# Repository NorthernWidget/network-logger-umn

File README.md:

Logger
======
This code is heavily based off the the Alog library by Northern Widget. When
completed, this implementation will include radio telemetry using the RFM69 chip
for RF communication. This library is currently a work in progress and should
not be expected to work on its own. Expect a working copy in early May.
The new libraries in this repo are the Network.* files.
-Luke Cesarz

Data logger library for the Arduino-based ALog (http://northernwidget.com/?page_id=8)

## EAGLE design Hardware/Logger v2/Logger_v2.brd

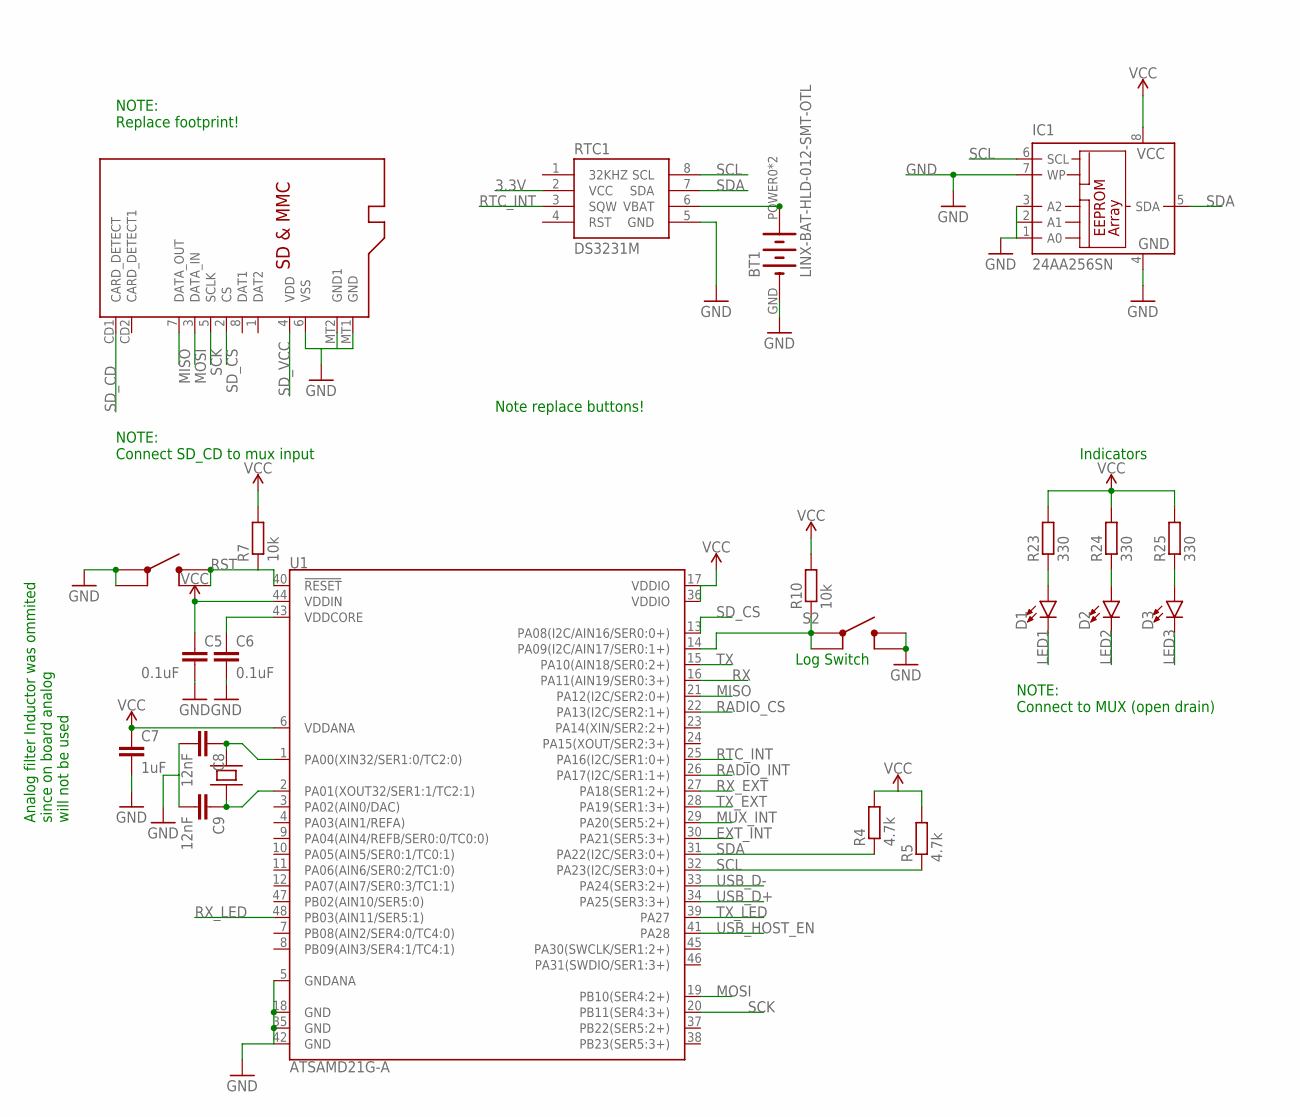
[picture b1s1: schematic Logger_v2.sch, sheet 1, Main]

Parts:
BT1: LINX-BAT-HLD-012-SMT-OTL; LINX_BAT-HLD-012-SMT
C5, C6: 0.1uF; C0603
C7: 1uF; C0603
C8, C9: 12nF; C0603
D1, D2, D3: LED0603; LED-0603
IC1: 24AA256SN; SO-08
R4, R5: 4.7k; R0603
R7, R10: 10k; R0603
R23, R24, R25: 330; R0603
RTC1: DS3231M; SO08
S2: SKRPABE010; SKRPABE010_(SWITCH)
U1: ATSAMD21G-A; TQFP-48
U$1: SKRPABE010; SKRPABE010_(SWITCH)
U$2: MICROSD
U$5: CM200; 4-SOJ

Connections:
3.3V: C5.1, C7.1, IC1.8 (VCC), R4.2, R5.2, R7.2, R10.2, R23.2, R24.2, R25.2, RTC1.2 (VCC), U1.6 (VDDANA), U1.17 (VDDIO), U1.36 (VDDIO), U1.44 (VDDIN); also elsewhere on the board
EXT_INT: U1.30 (PA21(SER5:3+)); also elsewhere on the board
GND: BT1.GND (-), C5.2, C6.2, C7.2, C8.2, C9.2, IC1.1 (A0), IC1.2 (A1), IC1.3 (A2), IC1.4 (GND), IC1.7 (WP), RTC1.5 (GND), S2.P$3 (3), S2.P$4 (4), U1.5 (GNDANA), U1.18 (GND), U1.35 (GND), U1.42 (GND), U$1.P$1 (1), U$1.P$2 (2), U$2.6 (VSS), U$2.MT1 (GND), U$2.MT2 (GND1); also elsewhere on the board
LED1: D1.C; also elsewhere on the board
LED2: D2.C; also elsewhere on the board
LED3: D3.C; also elsewhere on the board
MISO: U1.21 (PA12(I2C/SER2:0+)), U$2.7 (DATA_OUT); also elsewhere on the board
MOSI: U1.19 (PB10(SER4:2+)), U$2.3 (DATA_IN); also elsewhere on the board
MUX_INT: U1.29 (PA20(SER5:2+)); also elsewhere on the board
unnamed: R10.1, S2.P$1 (1), S2.P$2 (2), U1.14 (PA09(I2C/AIN17/SER0:1+))
unnamed: C6.1, U1.43 (VDDCORE)
unnamed: C8.1, U1.1 (PA00(XIN32/SER1:0/TC2:0)), U$5.P$4
unnamed: C9.1, U1.2 (PA01(XOUT32/SER1:1/TC2:1)), U$5.P$1
unnamed: BT1.POWER0 (+), BT1.POWER1 (+), RTC1.6 (VBAT)
unnamed: D1.A, R23.1
unnamed: D2.A, R24.1
unnamed: D3.A, R25.1
RADIO_CS: U1.22 (PA13(I2C/SER2:1+)); also elsewhere on the board
RADIO_INT: U1.26 (PA17(I2C/SER1:1+)); also elsewhere on the board
RST: R7.1, U1.40 (!RESET!), U$1.P$3 (3), U$1.P$4 (4); also elsewhere on the board
RTC_INT: RTC1.3 (SQW), U1.25 (PA16(I2C/SER1:0+))
RX: U1.16 (PA11(AIN19/SER0:3+))
RX_EXT: U1.27 (PA18(SER1:2+)); also elsewhere on the board
RX_LED: U1.48 (PB03(AIN11/SER5:1))
SCK: U1.20 (PB11(SER4:3+)), U$2.5 (SCLK); also elsewhere on the board
SCL: IC1.6 (SCL), R5.1, RTC1.8 (SCL), U1.32 (PA23(I2C/SER3:0+)); also elsewhere on the board
SDA: IC1.5 (SDA), R4.1, RTC1.7 (SDA), U1.31 (PA22(I2C/SER3:0+)); also elsewhere on the board
SD_CD: U$2.CD1 (CARD_DETECT)
SD_CS: U1.13 (PA08(I2C/AIN16/SER0:0+)), U$2.2 (CS)
SD_VCC: U$2.4 (VDD); also elsewhere on the board
TX: U1.15 (PA10(AIN18/SER0:2+))
TX_EXT: U1.28 (PA19(SER1:3+)); also elsewhere on the board
TX_LED: U1.39 (PA27)
USB_D+: U1.34 (PA25(SER3:3+)); also elsewhere on the board
USB_D-: U1.33 (PA24(SER3:2+)); also elsewhere on the board
USB_HOST_EN: U1.41 (PA28); also elsewhere on the board

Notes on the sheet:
NOTE: Replace footprint!
Log Switch
Analog filter Inductor was ommited since on board analog will not be used
Indicators
NOTE: Connect to MUX (open drain)
NOTE: Connect SD_CD to mux input
Note replace buttons!

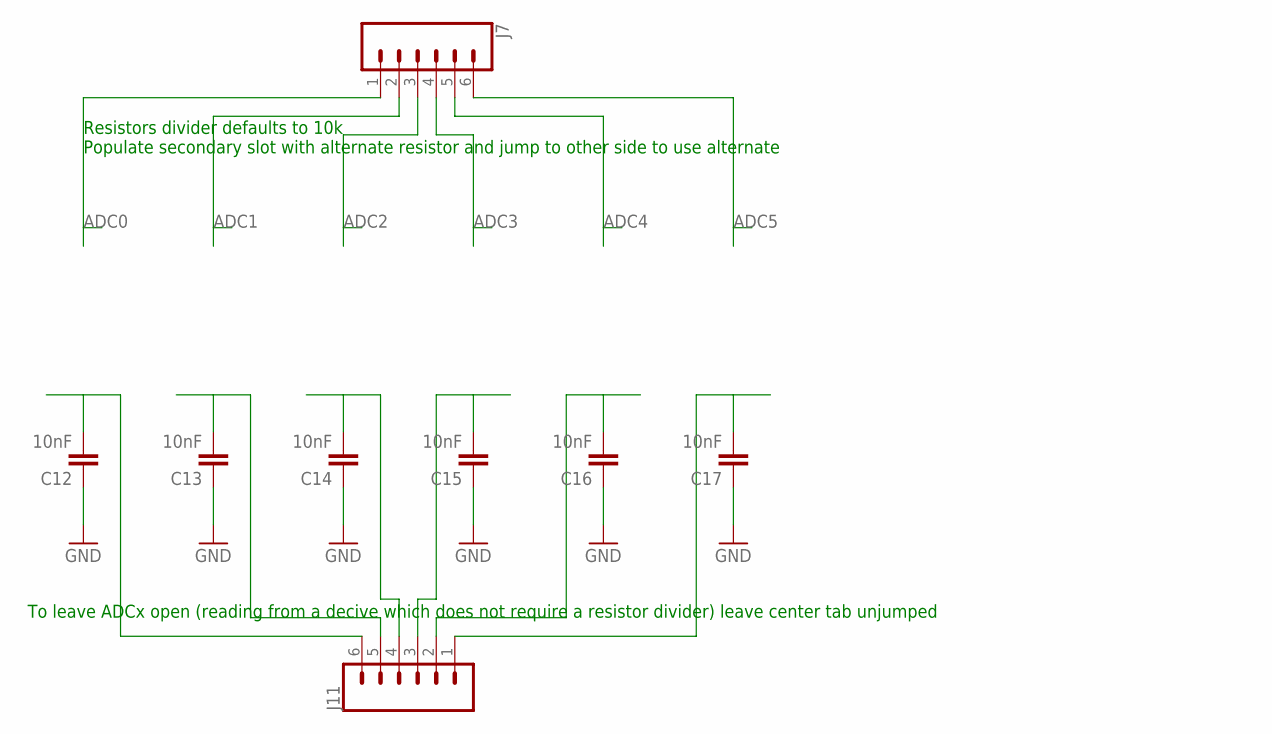
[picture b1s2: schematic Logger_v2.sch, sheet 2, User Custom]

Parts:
C12, C13, C14, C15, C16, C17: 10nF; C0603
J7, J11: CONN_06SMD-STRAIGHT-FEMALE; 1X06_SMD_STRAIGHT

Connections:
ADC0: J7.1; also elsewhere on the board
ADC1: J7.2; also elsewhere on the board
ADC2: J7.3; also elsewhere on the board
ADC3: J7.4; also elsewhere on the board
ADC4: J7.5; also elsewhere on the board
ADC5: J7.6; also elsewhere on the board
GND: C12.1, C13.1, C14.1, C15.1, C16.1, C17.1; also elsewhere on the board
unnamed: C12.2, J11.6
unnamed: C13.2, J11.5
unnamed: C14.2, J11.4
unnamed: C15.2, J11.3
unnamed: C16.2, J11.2
unnamed: C17.2, J11.1

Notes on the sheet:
Resistors divider defaults to 10k Populate secondary slot with alternate resistor and jump to other side to use alternate
To leave ADCx open (reading from a decive which does not require a resistor divider) leave center tab unjumped

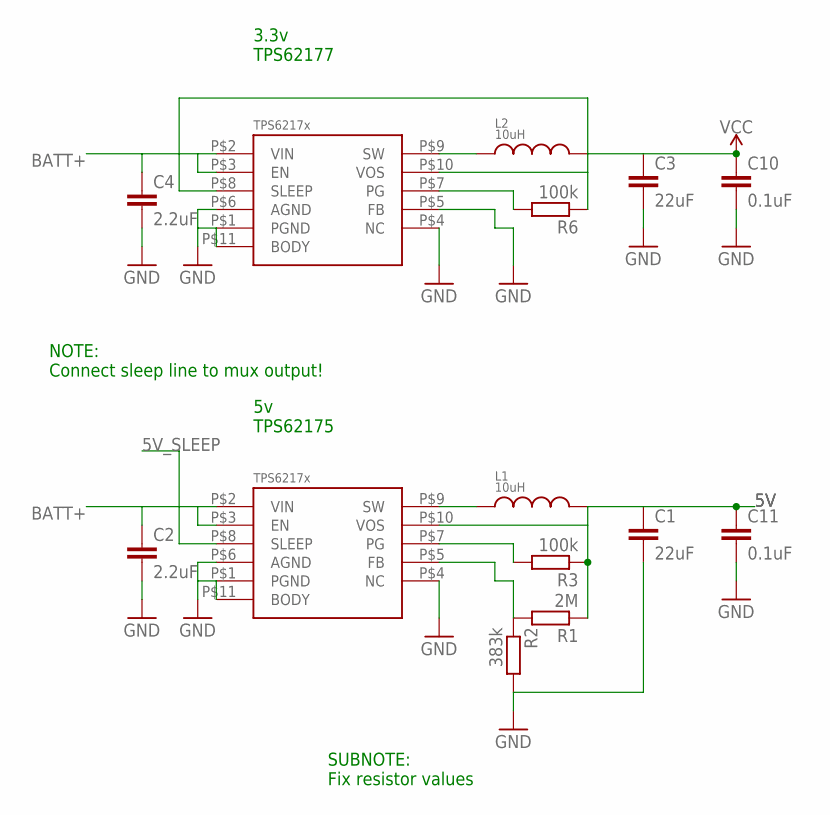
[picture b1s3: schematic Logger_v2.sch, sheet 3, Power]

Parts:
C1, C3: 22uF; C1210
C2, C4: 2.2uF; C0603
C10, C11: 0.1uF; C0603
L1, L2: 10uH; WE-LQS(INDUCTOR)
R1: 2M; R0603
R2: 383k; R0603
R3, R6: 100k; R0603
U$3, U$4: TPS6217X; WSON-10

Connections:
3.3V: C3.1, C10.1, L2.P$2, R6.1, U$4.P$8 (SLEEP), U$4.P$10 (VOS); also elsewhere on the board
5V: C1.1, C11.1, L1.P$2, R1.1, R3.1, U$3.P$10 (VOS); also elsewhere on the board
5V_SLEEP: U$3.P$8 (SLEEP)
BATT+: C2.1, C4.1, U$3.P$2 (VIN), U$3.P$3 (EN), U$4.P$2 (VIN), U$4.P$3 (EN); also elsewhere on the board
GND: C1.2, C2.2, C3.2, C4.2, C10.2, C11.2, R2.2, U$3.P$1 (PGND), U$3.P$4 (NC), U$3.P$6 (AGND), U$3.P$11 (BODY), U$4.P$1 (PGND), U$4.P$4 (NC), U$4.P$5 (FB), U$4.P$6 (AGND), U$4.P$11 (BODY); also elsewhere on the board
unnamed: L1.P$1, U$3.P$9 (SW)
unnamed: L2.P$1, U$4.P$9 (SW)
unnamed: R1.2, R2.1, U$3.P$5 (FB)
unnamed: R3.2, U$3.P$7 (PG)
unnamed: R6.2, U$4.P$7 (PG)

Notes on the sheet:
3.3v TPS62177
5v TPS62175
NOTE: Connect sleep line to mux output!
SUBNOTE: Fix resistor values

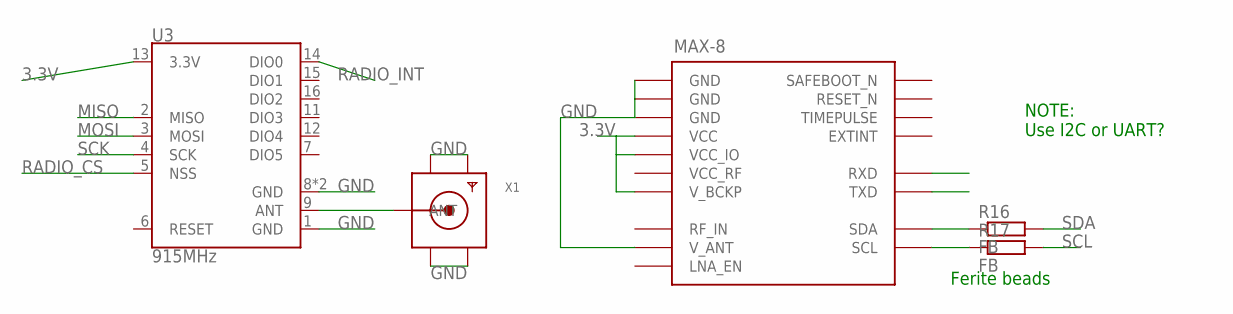
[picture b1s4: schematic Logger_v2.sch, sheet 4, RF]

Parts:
R16, R17: FB; R0603
U3: 915MHz; RFM69HCW-XXXS2
U$6: UBLOX_MAX-8; MAX-8
X1: SMACONNECTOR_EDGE; SMA_EDGELAUNCH

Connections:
3.3V: U3.13 (3.3V), U$6.P$6 (V_BCKP), U$6.P$7 (VCC_IO), U$6.P$8 (VCC); also elsewhere on the board
GND: U3.1 (GND), U3.8 (GND), U3.10 (GND), U$6.P$1 (GND), U$6.P$10 (GND), U$6.P$12 (GND), U$6.P$15 (V_ANT), X1.GND@1 (GND4), X1.GND@2 (GND3), X1.GND@3 (GND2), X1.GND@4 (GND1); also elsewhere on the board
MISO: U3.2 (MISO); also elsewhere on the board
MOSI: U3.3 (MOSI); also elsewhere on the board
unnamed: R16.1, U$6.P$16 (SDA)
unnamed: R17.1, U$6.P$17 (SCL)
unnamed: U3.9 (ANT), X1.P (ANT)
RADIO_CS: U3.5 (NSS); also elsewhere on the board
RADIO_INT: U3.14 (DIO0); also elsewhere on the board
SCK: U3.4 (SCK); also elsewhere on the board
SCL: R17.2; also elsewhere on the board
SDA: R16.2; also elsewhere on the board
VCC_RF: U$6.P$14 (VCC_RF)

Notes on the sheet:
NOTE: Use I2C or UART?
Ferite beads

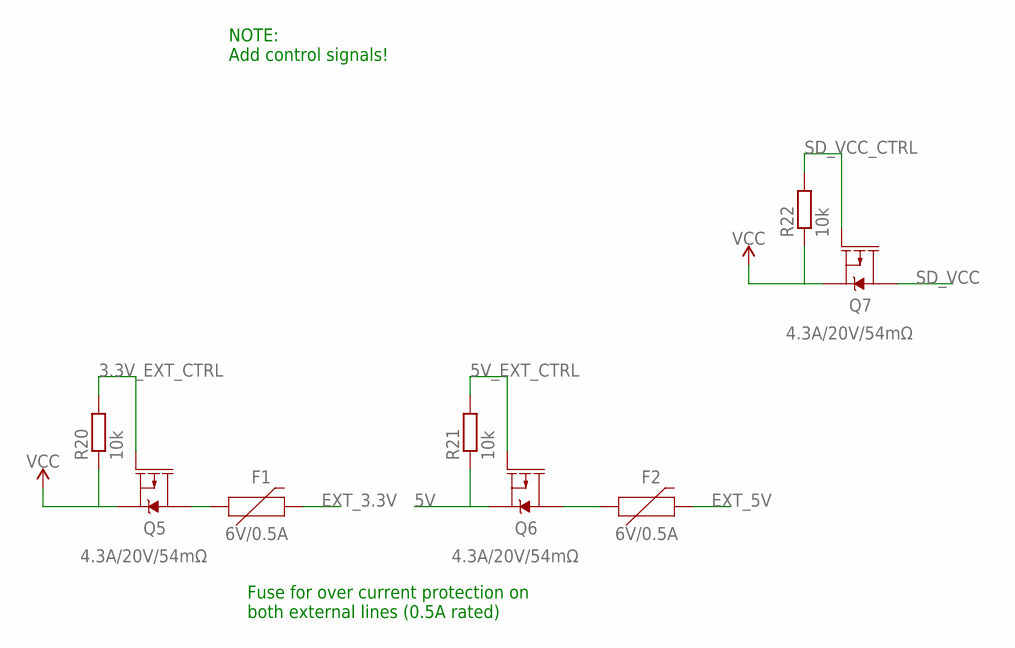
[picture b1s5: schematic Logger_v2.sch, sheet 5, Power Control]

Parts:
F1, F2: 6V/0.5A; 1206
Q5, Q6, Q7: 4.3A/20V/54mΩ; SOT23-3
R20, R21, R22: 10k; R0603

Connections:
3.3V: Q5.2 (S), Q7.2 (S), R20.1, R22.1; also elsewhere on the board
3.3V_EXT_CTRL: Q5.1 (G), R20.2; also elsewhere on the board
5V: Q6.2 (S), R21.1; also elsewhere on the board
5V_EXT_CTRL: Q6.1 (G), R21.2; also elsewhere on the board
EXT_3.3V: F1.2; also elsewhere on the board
EXT_5V: F2.2; also elsewhere on the board
unnamed: F1.1, Q5.3 (D)
unnamed: F2.1, Q6.3 (D)
SD_VCC: Q7.3 (D); also elsewhere on the board
SD_VCC_CTRL: Q7.1 (G), R22.2; also elsewhere on the board

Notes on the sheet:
NOTE: Add control signals!
Fuse for over current protection on both external lines (0.5A rated)

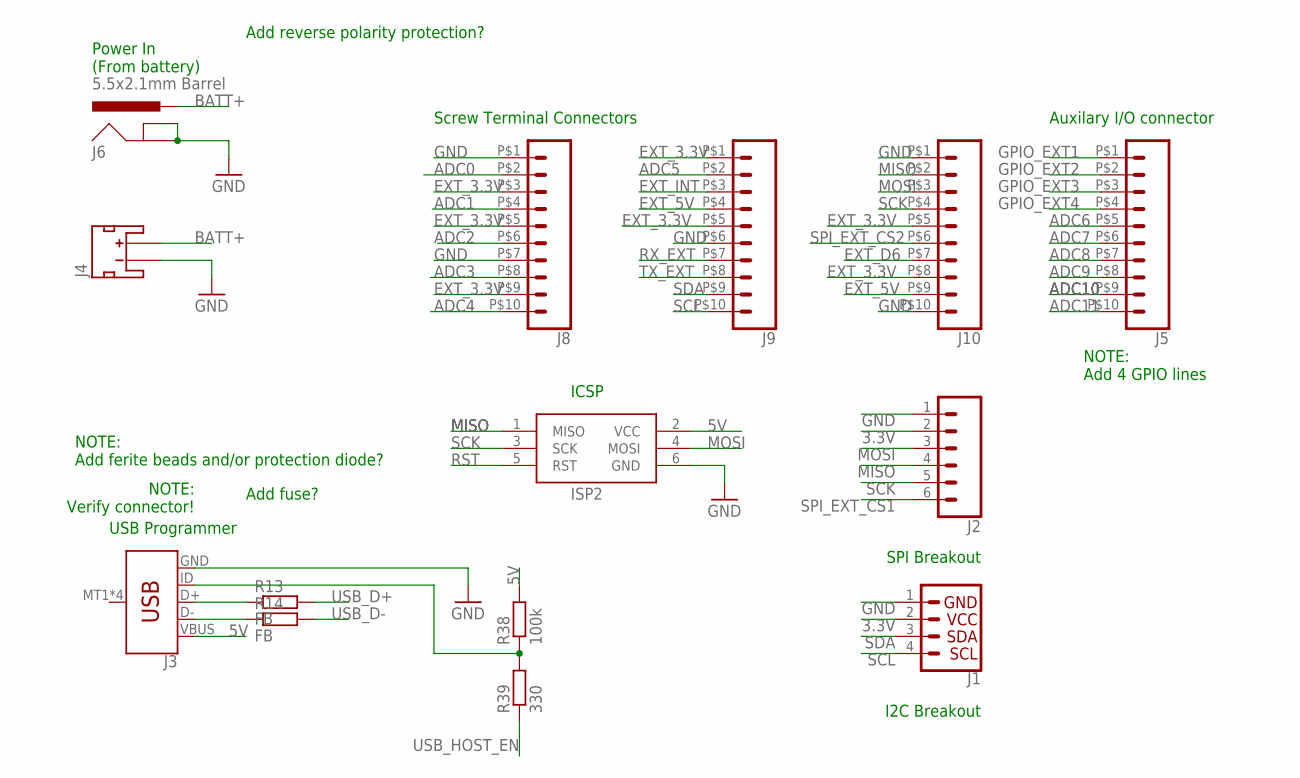
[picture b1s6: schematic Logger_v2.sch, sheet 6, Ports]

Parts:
ISP2: AVRISP-6; AVRISP
J1: I2C_STANDARD; 1X04
J2: CONN_06SILK_FEMALE_PTH; 1X06
J3: USB_MICRO-B_SMT; USB-MICROB
J4: JST_2MM_MALE; JST-2-SMD
J5, J8, J9, J10: CONN_10; SCREWTERMINAL-3.5MM-10
J6: 5.5x2.1mm Barrel; POWER_JACK_SMD
R13, R14: FB; R0603
R38: 100k; R0603
R39: 330; R0603

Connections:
3.3V: J1.2, J2.2; also elsewhere on the board
5V: ISP2.2 (VCC), J3.VBUS, R38.2; also elsewhere on the board
ADC0: J8.P$2 (2); also elsewhere on the board
ADC1: J8.P$4 (4); also elsewhere on the board
ADC2: J8.P$6 (6); also elsewhere on the board
ADC3: J8.P$8 (8); also elsewhere on the board
ADC4: J8.P$10 (10); also elsewhere on the board
ADC5: J9.P$2 (2); also elsewhere on the board
ADC6: J5.P$5 (5); also elsewhere on the board
ADC7: J5.P$6 (6); also elsewhere on the board
ADC8: J5.P$7 (7); also elsewhere on the board
ADC9: J5.P$8 (8); also elsewhere on the board
ADC10: J5.P$9 (9); also elsewhere on the board
ADC11: J5.P$10 (10); also elsewhere on the board
BATT+: J4.2 (+), J6.VIN0 (PWR); also elsewhere on the board
EXT_3.3V: J8.P$3 (3), J8.P$5 (5), J8.P$9 (9), J9.P$1 (1), J9.P$5 (5), J10.P$5 (5), J10.P$8 (8); also elsewhere on the board
EXT_5V: J9.P$4 (4), J10.P$9 (9); also elsewhere on the board
EXT_D6: J10.P$7 (7); also elsewhere on the board
EXT_INT: J9.P$3 (3); also elsewhere on the board
GND: ISP2.6 (GND), J1.1, J2.1, J3.GND, J4.1 (-), J6.GND (GNDBREAK), J6.P$4 (GND), J8.P$1 (1), J8.P$7 (7), J9.P$6 (6), J10.P$1 (1), J10.P$10 (10); also elsewhere on the board
GPIO_EXT1: J5.P$1 (1); also elsewhere on the board
GPIO_EXT2: J5.P$2 (2); also elsewhere on the board
GPIO_EXT3: J5.P$3 (3); also elsewhere on the board
GPIO_EXT4: J5.P$4 (4); also elsewhere on the board
MISO: ISP2.1 (MISO), J2.4, J10.P$2 (2); also elsewhere on the board
MOSI: ISP2.4 (MOSI), J2.3, J10.P$3 (3); also elsewhere on the board
unnamed: J3.D+, R13.1
unnamed: J3.D-, R14.1
unnamed: J3.ID, R38.1, R39.2
RST: ISP2.5 (RST); also elsewhere on the board
RX_EXT: J9.P$7 (7); also elsewhere on the board
SCK: ISP2.3 (SCK), J2.5, J10.P$4 (4); also elsewhere on the board
SCL: J1.4, J9.P$10 (10); also elsewhere on the board
SDA: J1.3, J9.P$9 (9); also elsewhere on the board
SPI_EXT_CS1: J2.6; also elsewhere on the board
SPI_EXT_CS2: J10.P$6 (6); also elsewhere on the board
TX_EXT: J9.P$8 (8); also elsewhere on the board
USB_D+: R13.2; also elsewhere on the board
USB_D-: R14.2; also elsewhere on the board
USB_HOST_EN: R39.1; also elsewhere on the board

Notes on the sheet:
Power In (From battery)
Add reverse polarity protection?
I2C Breakout
SPI Breakout
NOTE: Verify connector!
Add fuse?
NOTE: Add ferite beads and/or protection diode?
Screw Terminal Connectors
ICSP
USB Programmer
Auxilary I/O connector
NOTE: Add 4 GPIO lines

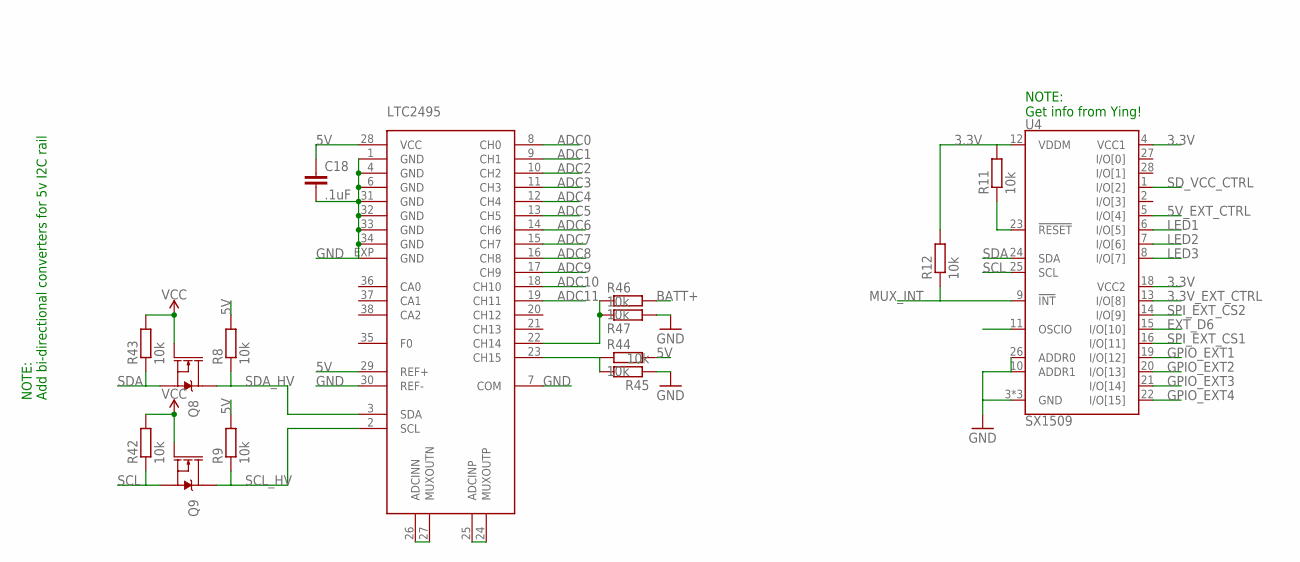
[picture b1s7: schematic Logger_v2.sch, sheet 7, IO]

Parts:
C18: .1uF; C0603
Q8, Q9: 220mA/50V/3.5Ω; SOT23-3
R8, R9, R11, R12, R42, R43, R44, R45, R46, R47: 10k; R0603
U4: SX1509; QFN-28
U$7: LTC2495; QFN38-5X7

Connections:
3.3V: Q8.1 (G), Q9.1 (G), R11.2, R12.2, R42.2, R43.2, U4.4 (VCC1), U4.12 (VDDM), U4.18 (VCC2); also elsewhere on the board
3.3V_EXT_CTRL: U4.13 (I/O[8]); also elsewhere on the board
5V: C18.1, R8.2, R9.2, R44.2, U$7.28 (VCC), U$7.29 (REF+); also elsewhere on the board
5V_EXT_CTRL: U4.5 (I/O[4]); also elsewhere on the board
ADC0: U$7.8 (CH0); also elsewhere on the board
ADC1: U$7.9 (CH1); also elsewhere on the board
ADC2: U$7.10 (CH2); also elsewhere on the board
ADC3: U$7.11 (CH3); also elsewhere on the board
ADC4: U$7.12 (CH4); also elsewhere on the board
ADC5: U$7.13 (CH5); also elsewhere on the board
ADC6: U$7.14 (CH6); also elsewhere on the board
ADC7: U$7.15 (CH7); also elsewhere on the board
ADC8: U$7.16 (CH8); also elsewhere on the board
ADC9: U$7.17 (CH9); also elsewhere on the board
ADC10: U$7.18 (CH10); also elsewhere on the board
ADC11: U$7.19 (CH11); also elsewhere on the board
BATT+: R46.2; also elsewhere on the board
EXT_D6: U4.15 (I/O[10]); also elsewhere on the board
GND: C18.2, R45.1, R47.2, U4.3 (GND), U4.10 (ADDR1), U4.17 (GND), U4.26 (ADDR0), U4.29 (GND), U$7.1 (GND), U$7.4 (GND), U$7.6 (GND), U$7.7 (COM), U$7.30 (REF-), U$7.31 (GND), U$7.32 (GND), U$7.33 (GND), U$7.34 (GND), U$7.EXP (GND); also elsewhere on the board
GPIO_EXT1: U4.19 (I/O[12]); also elsewhere on the board
GPIO_EXT2: U4.20 (I/O[13]); also elsewhere on the board
GPIO_EXT3: U4.21 (I/O[14]); also elsewhere on the board
GPIO_EXT4: U4.22 (I/O[15]); also elsewhere on the board
LED1: U4.6 (I/O[5]); also elsewhere on the board
LED2: U4.7 (I/O[6]); also elsewhere on the board
LED3: U4.8 (I/O[7]); also elsewhere on the board
MUX_INT: R12.1, U4.9 (!INT); also elsewhere on the board
unnamed: U$7.26 (ADCINN), U$7.27 (MUXOUTN)
unnamed: U$7.24 (MUXOUTP), U$7.25 (ADCINP)
unnamed: R44.1, R45.2, U$7.23 (CH15)
unnamed: R46.1, R47.1, U$7.22 (CH14)
unnamed: R11.1, U4.23 (!RESET)
SCL: Q9.2 (S), R42.1, U4.25 (SCL); also elsewhere on the board
SCL_HV: Q9.3 (D), R9.1, U$7.2 (SCL)
SDA: Q8.2 (S), R43.1, U4.24 (SDA); also elsewhere on the board
SDA_HV: Q8.3 (D), R8.1, U$7.3 (SDA)
SD_VCC_CTRL: U4.1 (I/O[2]); also elsewhere on the board
SPI_EXT_CS1: U4.16 (I/O[11]); also elsewhere on the board
SPI_EXT_CS2: U4.14 (I/O[9]); also elsewhere on the board

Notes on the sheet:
NOTE: Add bi-directional converters for 5v I2C rail
NOTE: Get info from Ying!

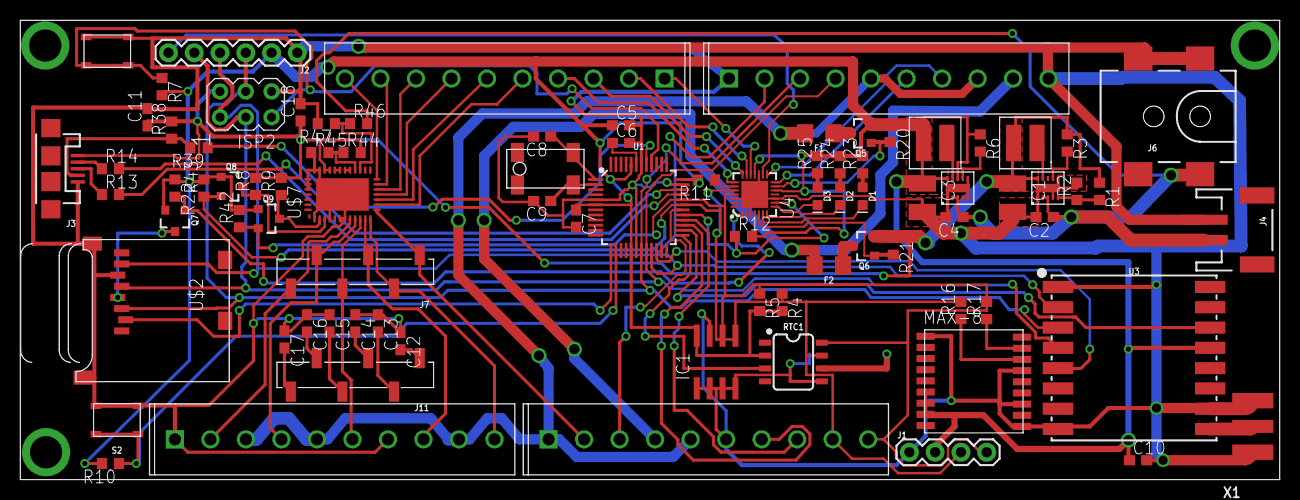
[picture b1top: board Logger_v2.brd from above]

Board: 2 copper layers, 124.1 x 45.3 mm, 87 parts (1 on the bottom side), 83 nets.

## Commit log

2017-02-04 Bringing together all the code.
2017-02-04 Bringing together all the code2.
2017-02-04 added some functions and such. Need to read ds
2017-02-07 radio chip library added
2017-02-15 change example
2017-02-15 edit example
2017-02-16 moved file
2017-02-17 added tex doc from earlier
2017-02-17 Initial conclusion writeup
2017-02-17 Why our team is right for you
2017-02-17 One more conclusion line for good measure
2017-02-22 Added Hardware section and moddified RFM69 Example
    Added a hardware folder and moved work from existing git hardware section into this, will move current eagle work into this section soon. Also made changes to the example file for thr RFM69
2017-03-08 cleanup, moved design proposal to google drive folder - luke
2017-03-09 added r_tests for collions
2017-03-11 Updated readme - Luke
2017-03-12 read and send packet, added variables
2017-03-12 preliminary network functions added, Luke & Jeff
2017-03-19 Formatting Fix -Luke
2017-03-19 Added queue and packet class files. Some cleaning -Luke
2017-03-19 formatting Queue files
2017-03-19 received packet and runNetwork added -Luke & Jeff
2017-03-19 queue max size and return values Jeff
2017-03-21 Added logger schematic
    Added the schematic for the logger, this is rough, still a work in progress, but I wanted to get the version control going asap. Also added prototype dev board files
2017-03-29 simple run network Jeff
2017-03-30 wrote the baseline for the new & improved runNetwork. Lots of TODO's in it still. Mostly just need to figure out timeout stuff
2017-03-30 PCB Complete, Ready for Checking
    PCB is functionally complete, ready for double checking and verification.
    Note: Still should switch battery clip
2017-03-30 small addition to runNetwork (reconnect to coord & dropped coord timeout)
2017-03-31 fixed memory leak Jeff
2017-03-31 finished receivedPacket() and added droppedCoord()
2017-03-31 Updated readme to include description of the new network algorithm
2017-04-01 PCB Major Issues Fixed
    All major issues on the PCB are fixed and only remaining problems are with solder mask spacing. Ready for final functional check
2017-04-02 timeout adjustments -luke & david
2017-04-02 testing0
2017-04-02 Testing with david and lukemdukem
2017-04-06 More testing, have self discovery working, need to fix crash & test multiple radios
2017-04-07 Final PCB Logger Design
    The final design iteration for the logger PCB
2017-04-07 added debug statements
2017-04-07 debugging statements, Jeff
2017-04-07 minor changes, fix for zero, Jeff
2017-04-10 bug fixes, Jeff
2017-04-10 small insignifigant changes, Jeff
2017-04-12 Added complete battery board schematic
    Added a complete and functional schematic for the battery board, revisions still pending should be functional
2017-04-12 minor testing changes, Jeff
2017-04-12 pulling changes
2017-04-13 alpha version
2017-04-13 working testing code, Jeff
2017-04-13 testing changes
2017-04-28 Testing pre branch for feather
2017-04-28 added RH lib
2017-04-28 change includes
2017-04-28 fixed
2017-04-28 auwhrkvjas
2017-04-28 inclues
2017-04-29 added acking and made addressing relevant
2017-04-29 small changes
2017-04-30 Debugging, network & feather working no RSSI
2017-04-30 cleaned out library
2017-04-30 fix timing for send and rssi
2017-05-01 github being dumb (removing and re-adding the same file)
2017-05-01 using reliabledatagram
2017-05-01 editcoord/sender
2017-05-01 fixed 0 address error
2017-05-01 unfinished demo
2017-05-03 loop on failure, fix
2017-05-03 feather lib comments

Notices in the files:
parts and their libraries:
SparkFun-LED: Licensing: Creative Commons ShareAlike 4.0 International - https://creativecommons.org/licenses/by-sa/4.0
